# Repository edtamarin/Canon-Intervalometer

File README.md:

# DeltaShot

This is an intervalometer based on an ESP32 for remote shutter control of a DLSR camera. Currently the device is built for Canon bodies.

## Features

The Canon bodies are triggered by shorting the focus or the shutter pin to ground. Older versions use an N3 connector whereas newer ones use a standard jack.

The DeltaShot offers a 3.5mm jack output to interface with the camera. It is possible to trigger the camera manually at all times using two pushbutton switches on the device. However, these switches can also be triggered using the onboard ESP32 controller.

The software for the ESP32 is currently in development.

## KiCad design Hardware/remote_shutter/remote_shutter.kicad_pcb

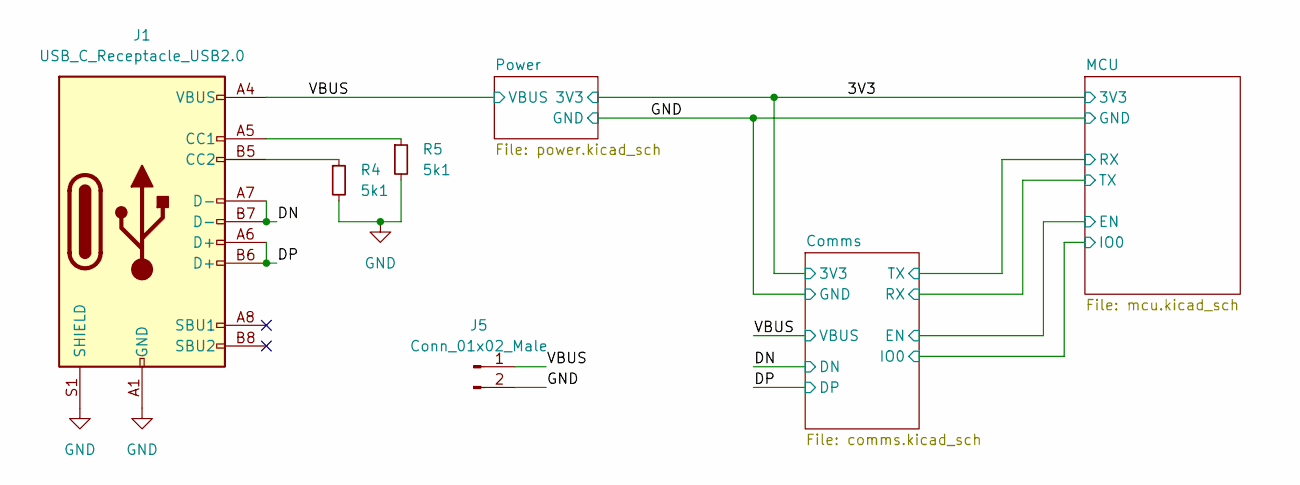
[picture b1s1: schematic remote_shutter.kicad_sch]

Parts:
J1: USB_C_Receptacle_USB2.0; USB_C_Receptacle_XKB_U262-16XN-4BVC11
J5: Conn_01x02_Male; PinHeader_1x02_P2.54mm_Vertical
R4, R5: 5k1; R_0603_1608Metric_Pad0.98x0.95mm_HandSolder

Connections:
/DN: J1.A7 (D-), J1.B7 (D-); also elsewhere on the board
/DP: J1.A6 (D+), J1.B6 (D+); also elsewhere on the board
/VBUS: J1.A4 (VBUS), J1.A9 (VBUS), J1.B4 (VBUS), J1.B9 (VBUS), J5.1; also elsewhere on the board
GND: J1.A1 (GND), J1.A12 (GND), J1.B1 (GND), J1.B12 (GND), J1.S1 (SHIELD), J5.2, R4.2, R5.2; also elsewhere on the board
unnamed: J1.A5 (CC1), R5.1
unnamed: J1.B5 (CC2), R4.1

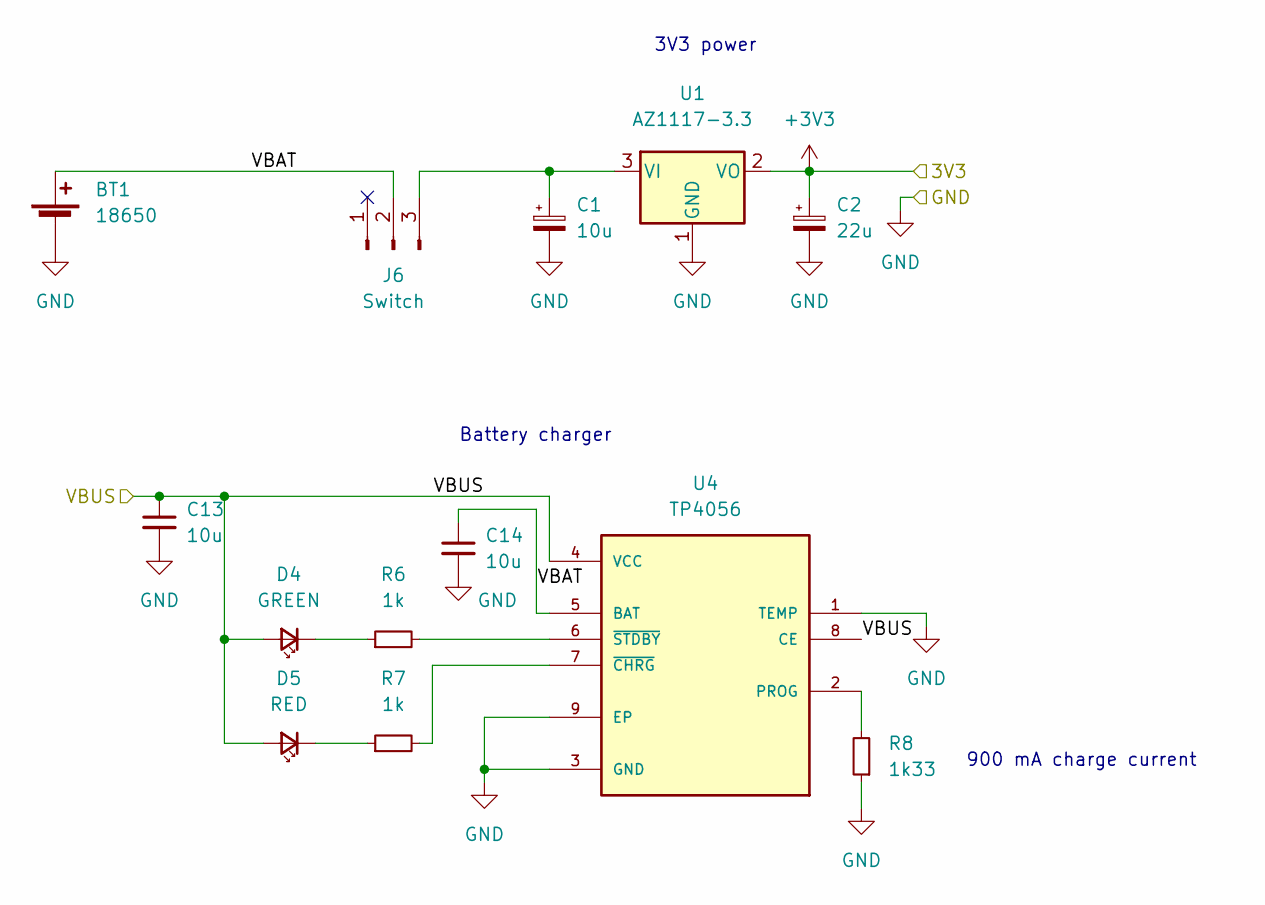
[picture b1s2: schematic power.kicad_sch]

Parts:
BT1: 18650; PinHeader_1x02_P2.54mm_Vertical
C1: 10u; CP_EIA-3528-21_Kemet-B_Pad1.50x2.35mm_HandSolder
C2: 22u; CP_EIA-3528-21_Kemet-B_Pad1.50x2.35mm_HandSolder
C13, C14: 10u; C_0805_2012Metric_Pad1.18x1.45mm_HandSolder
D4: GREEN; LED_0603_1608Metric_Pad1.05x0.95mm_HandSolder
D5: RED; LED_0603_1608Metric_Pad1.05x0.95mm_HandSolder
J6: Switch; PinHeader_1x03_P2.54mm_Vertical
R6, R7: 1k; R_0603_1608Metric_Pad0.98x0.95mm_HandSolder
R8: 1k33; R_0603_1608Metric_Pad0.98x0.95mm_HandSolder
U1: AZ1117-3.3; SOT-223-3_TabPin2
U4: TP4056; SOP127P600X175-9N

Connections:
+3V3: C2.1, U1.2 (VO); also elsewhere on the board
/Power/VBAT: BT1.1 (+), C14.1, J6.2, U4.5 (BAT)
/VBUS: C13.1, D4.2 (A), D5.2 (A), U4.4 (VCC), U4.8 (CE); also elsewhere on the board
GND: BT1.2 (-), C1.2, C2.2, C13.2, C14.2, R8.1, U1.1 (GND), U4.1 (TEMP), U4.3 (GND), U4.9 (EP); also elsewhere on the board
unnamed: C1.1, J6.3, U1.3 (VI)
unnamed: D4.1 (K), R6.1
unnamed: D5.1 (K), R7.1
unnamed: R6.2, U4.6 (~STDBY)
unnamed: R7.2, U4.7 (~CHRG)
unnamed: R8.2, U4.2 (PROG)

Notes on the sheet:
3V3 power
900 mA charge current
Battery charger

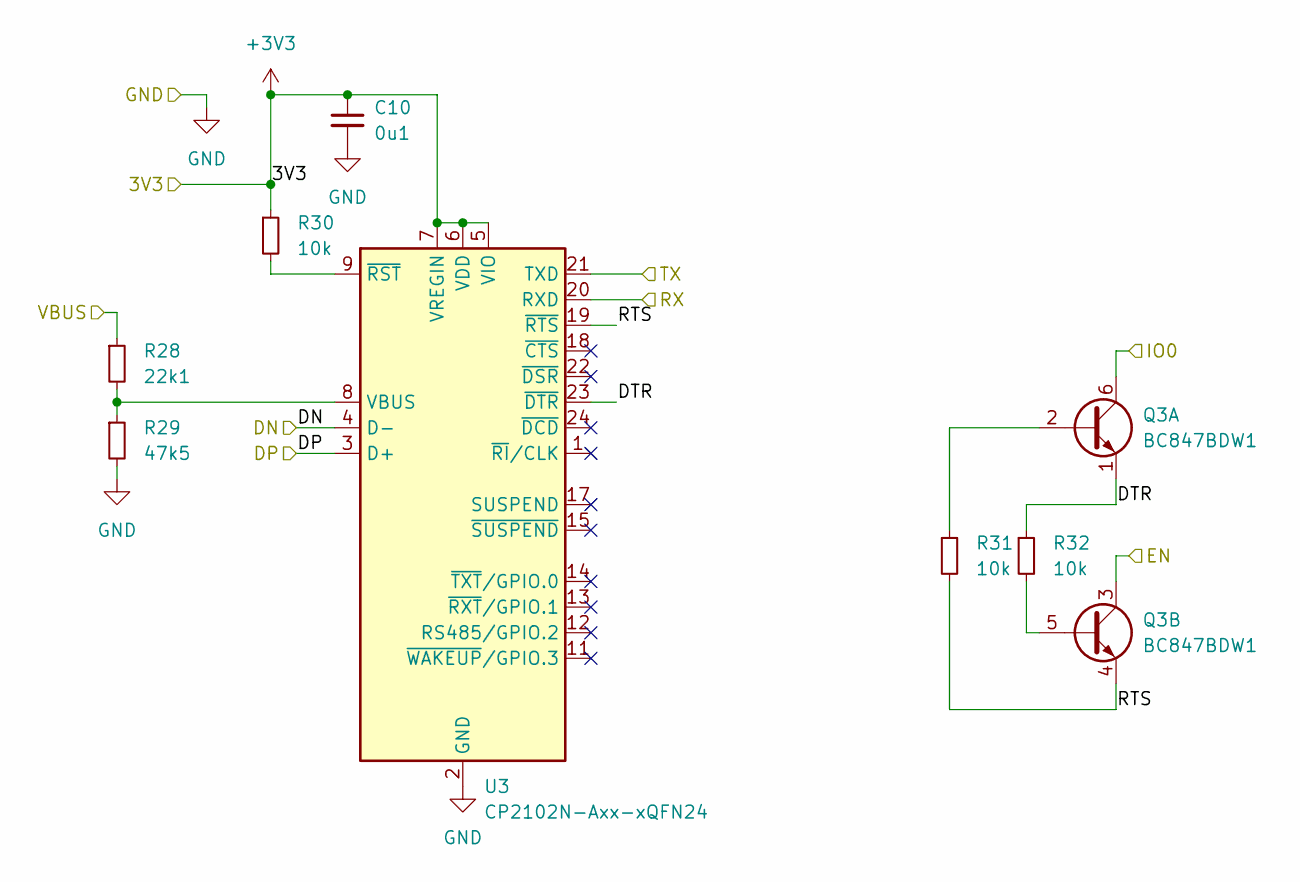
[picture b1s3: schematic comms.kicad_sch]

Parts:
C10: 0u1; C_0603_1608Metric_Pad1.08x0.95mm_HandSolder
Q3: BC847BDW1; SOT-363_SC-70-6
R28: 22k1; R_0603_1608Metric_Pad0.98x0.95mm_HandSolder
R29: 47k5; R_0603_1608Metric_Pad0.98x0.95mm_HandSolder
R30, R31, R32: 10k; R_0603_1608Metric_Pad0.98x0.95mm_HandSolder
U3: CP2102N-Axx-xQFN24; QFN-24-1EP_4x4mm_P0.5mm_EP2.6x2.6mm

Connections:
+3V3: C10.1, R30.1, U3.5 (VIO), U3.6 (VDD), U3.7 (VREGIN); also elsewhere on the board
/Comms/DTR: Q3.1 (E1), R32.1, U3.23 (~DTR)
/Comms/RTS: Q3.4 (E2), R31.2, U3.19 (~RTS)
/DN: U3.4 (D-); also elsewhere on the board
/DP: U3.3 (D+); also elsewhere on the board
/MCU/EN: Q3.3 (C2); also elsewhere on the board
/MCU/IO0: Q3.6 (C1); also elsewhere on the board
/MCU/RX: U3.21 (TXD); also elsewhere on the board
/MCU/TX: U3.20 (RXD); also elsewhere on the board
/VBUS: R28.1; also elsewhere on the board
GND: C10.2, R29.2, U3.2 (GND), U3.25 (GND); also elsewhere on the board
unnamed: Q3.2 (B1), R31.1
unnamed: Q3.5 (B2), R32.2
unnamed: R28.2, R29.1, U3.8 (VBUS)
unnamed: R30.2, U3.9 (~RST)

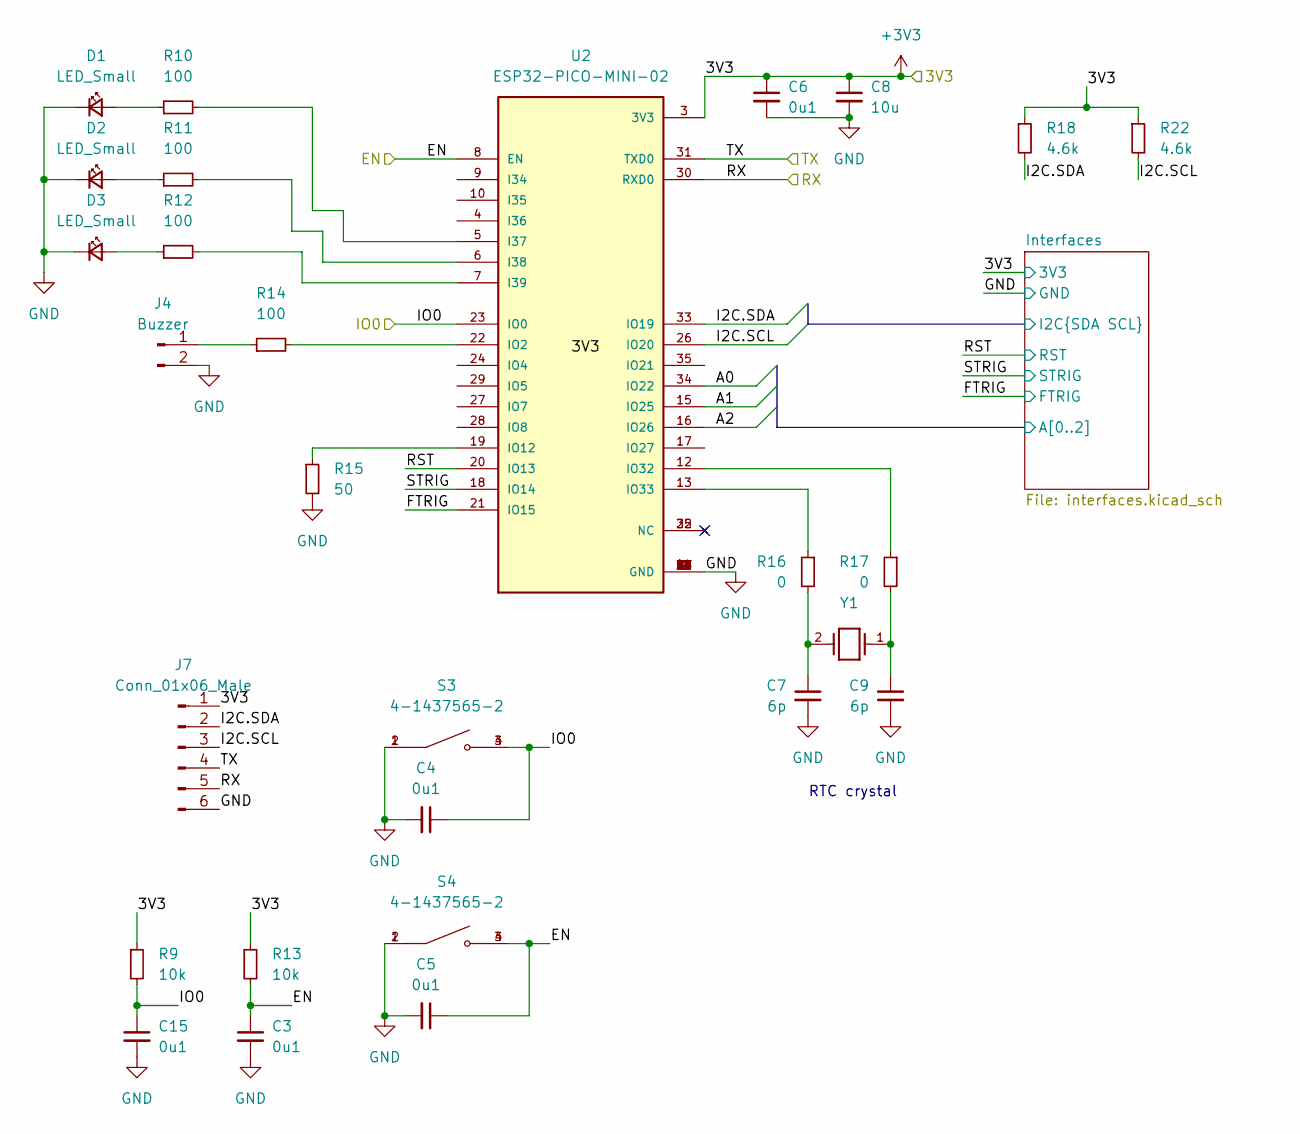
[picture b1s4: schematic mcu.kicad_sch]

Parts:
C3, C4, C5, C6, C15: 0u1; C_0603_1608Metric_Pad1.08x0.95mm_HandSolder
C7, C9: 6p; C_0603_1608Metric_Pad1.08x0.95mm_HandSolder
C8: 10u; C_0805_2012Metric_Pad1.18x1.45mm_HandSolder
D1, D2, D3: LED_Small; LED_0603_1608Metric_Pad1.05x0.95mm_HandSolder
J4: Buzzer; PinSocket_1x02_P2.54mm_Vertical
J7: Conn_01x06_Male; PinHeader_1x06_P2.54mm_Vertical
R9, R13: 10k; R_0603_1608Metric_Pad0.98x0.95mm_HandSolder
R10, R11, R12, R14: 100; R_0603_1608Metric_Pad0.98x0.95mm_HandSolder
R15: 50; R_0603_1608Metric_Pad0.98x0.95mm_HandSolder
R16, R17: 0; R_0603_1608Metric_Pad0.98x0.95mm_HandSolder
R18, R22: 4.6k; R_0603_1608Metric_Pad0.98x0.95mm_HandSolder
S3, S4: 4-1437565-2; SW_4-1437565-2
U2: ESP32-PICO-MINI-02; MODULE_ESP32-PICO-MINI-02; PARTREV v1.0
Y1: NX3215SA-32.768K-STD-MUA-14; XTAL_NX3215SA-32.768K-STD-MUA-14; PARTREV --

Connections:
+3V3: C6.1, C8.1, J7.1, R9.1, R13.1, R18.1, R22.1, U2.3 (3V3); also elsewhere on the board
/MCU/EN: C3.1, C5.1, R13.2, S4.3, S4.4, U2.8 (EN); also elsewhere on the board
/MCU/FTRIG: U2.21 (IO15); also elsewhere on the board
/MCU/IO0: C4.1, C15.1, R9.2, S3.3, S3.4, U2.23 (IO0); also elsewhere on the board
/MCU/Interfaces/A0: U2.34 (IO22); also elsewhere on the board
/MCU/Interfaces/A1: U2.15 (IO25); also elsewhere on the board
/MCU/Interfaces/A2: U2.16 (IO26); also elsewhere on the board
/MCU/Interfaces/I2C.SCL: J7.3, R22.2, U2.26 (IO20); also elsewhere on the board
/MCU/Interfaces/I2C.SDA: J7.2, R18.2, U2.33 (IO19); also elsewhere on the board
/MCU/RST: U2.20 (IO13); also elsewhere on the board
/MCU/RX: J7.5, U2.30 (RXD0); also elsewhere on the board
/MCU/STRIG: U2.18 (IO14); also elsewhere on the board
/MCU/TX: J7.4, U2.31 (TXD0); also elsewhere on the board
GND: C3.2, C4.2, C5.2, C6.2, C7.2, C8.2, C9.2, C15.2, D1.1 (K), D2.1 (K), D3.1 (K), J4.2, J7.6, R15.2, S3.1, S3.2, S4.1, S4.2, U2.1 (GND), U2.2 (GND), U2.11 (GND), U2.14 (GND), U2.36 (GND), U2.37 (GND), U2.38 (GND), U2.39 (GND), U2.40 (GND), U2.41 (GND), U2.42 (GND), U2.43 (GND), U2.44 (GND), U2.45 (GND), U2.46 (GND), U2.47 (GND), U2.48 (GND), U2.49 (GND), U2.50 (GND), U2.51 (GND), U2.52 (GND), U2.53 (GND), U2.54 (GND), U2.55 (GND), U2.56 (GND), U2.57 (GND), U2.58 (GND), U2.59 (GND), U2.60 (GND), U2.61 (GND); also elsewhere on the board
unnamed: C7.1, R16.2, Y1.2
unnamed: C9.1, R17.2, Y1.1
unnamed: D1.2 (A), R10.1
unnamed: D2.2 (A), R11.1
unnamed: D3.2 (A), R12.1
unnamed: J4.1, R14.1
unnamed: R10.2, U2.5 (I37)
unnamed: R11.2, U2.6 (I38)
unnamed: R12.2, U2.7 (I39)
unnamed: R14.2, U2.22 (IO2)
unnamed: R15.1, U2.19 (IO12)
unnamed: R16.1, U2.13 (IO33)
unnamed: R17.1, U2.12 (IO32)

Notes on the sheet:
RTC crystal

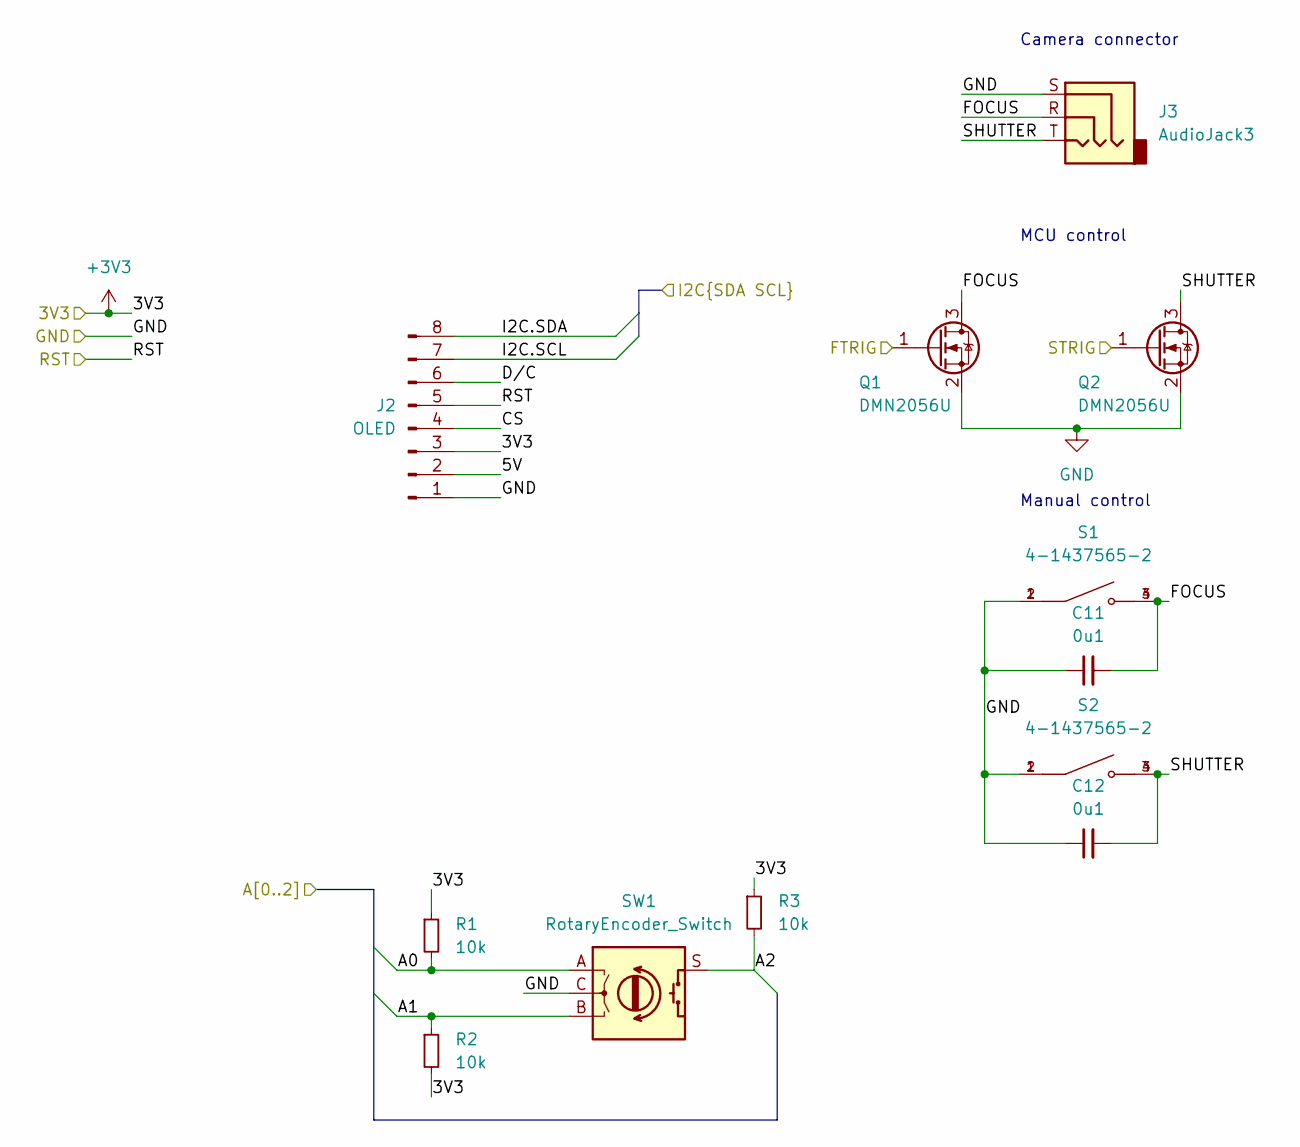
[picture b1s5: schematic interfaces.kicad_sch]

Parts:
C11, C12: 0u1; C_0603_1608Metric_Pad1.08x0.95mm_HandSolder
J2: OLED; PinSocket_1x08_P2.54mm_Vertical
J3: AudioJack3; PJ-320B
Q1, Q2: DMN2056U; SOT-23
R1, R2, R3: 10k; R_0603_1608Metric_Pad0.98x0.95mm_HandSolder
S1, S2: 4-1437565-2; SW_4-1437565-2
SW1: RotaryEncoder_Switch; SIQ-02FVS3

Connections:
+3V3: J2.3, R1.1, R2.2, R3.1; also elsewhere on the board
/MCU/FTRIG: Q1.1 (G); also elsewhere on the board
/MCU/Interfaces/5V: J2.2
/MCU/Interfaces/A0: R1.2, SW1.A; also elsewhere on the board
/MCU/Interfaces/A1: R2.1, SW1.B; also elsewhere on the board
/MCU/Interfaces/A2: R3.2, SW1.S; also elsewhere on the board
/MCU/Interfaces/CS: J2.4
/MCU/Interfaces/D/C: J2.6
/MCU/Interfaces/FOCUS: C11.2, J3.R, Q1.3 (D), S1.3, S1.4
/MCU/Interfaces/I2C.SCL: J2.7; also elsewhere on the board
/MCU/Interfaces/I2C.SDA: J2.8; also elsewhere on the board
/MCU/Interfaces/SHUTTER: C12.2, J3.T, Q2.3 (D), S2.3, S2.4
/MCU/RST: J2.5; also elsewhere on the board
/MCU/STRIG: Q2.1 (G); also elsewhere on the board
GND: C11.1, C12.1, J2.1, J3.S, Q1.2 (S), Q2.2 (S), S1.1, S1.2, S2.1, S2.2, SW1.C; also elsewhere on the board

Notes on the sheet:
MCU control
Manual control
Camera connector

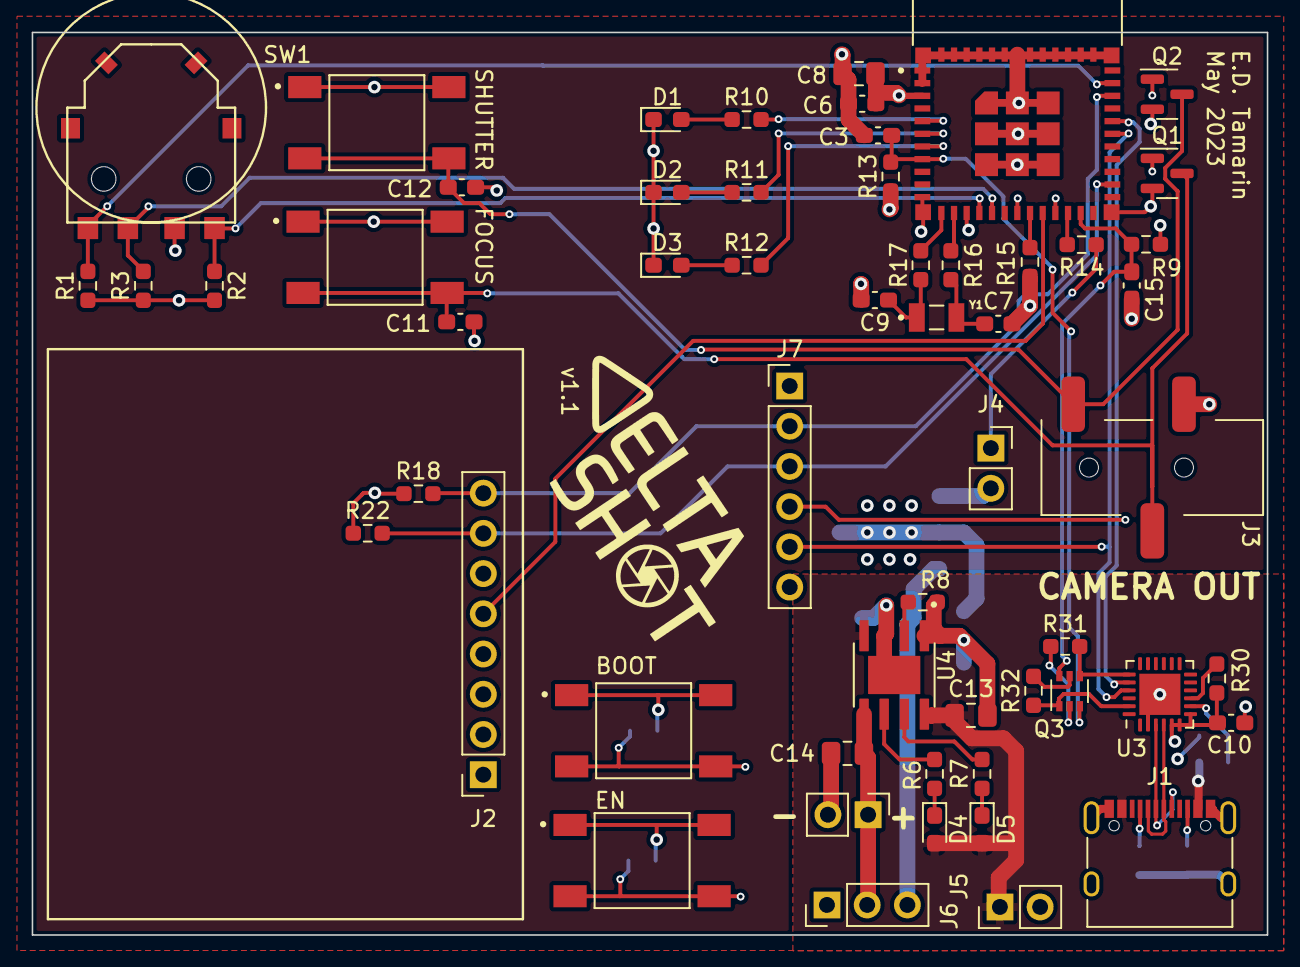
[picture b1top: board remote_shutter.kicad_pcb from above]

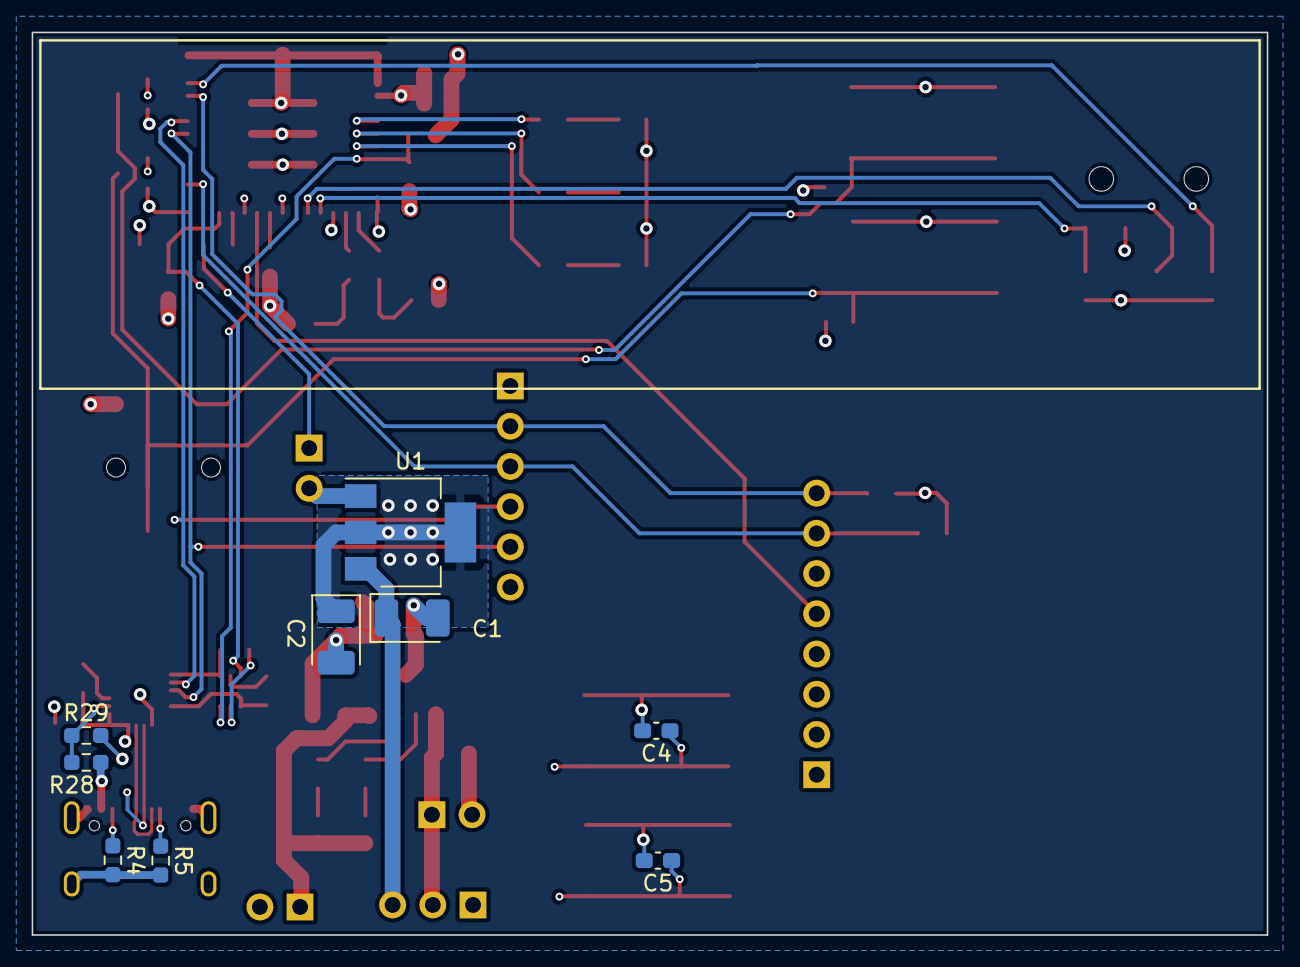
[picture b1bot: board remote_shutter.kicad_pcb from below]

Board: 4 copper layers, 78.0 x 57.0 mm, 65 parts (9 on the bottom side), 47 nets.

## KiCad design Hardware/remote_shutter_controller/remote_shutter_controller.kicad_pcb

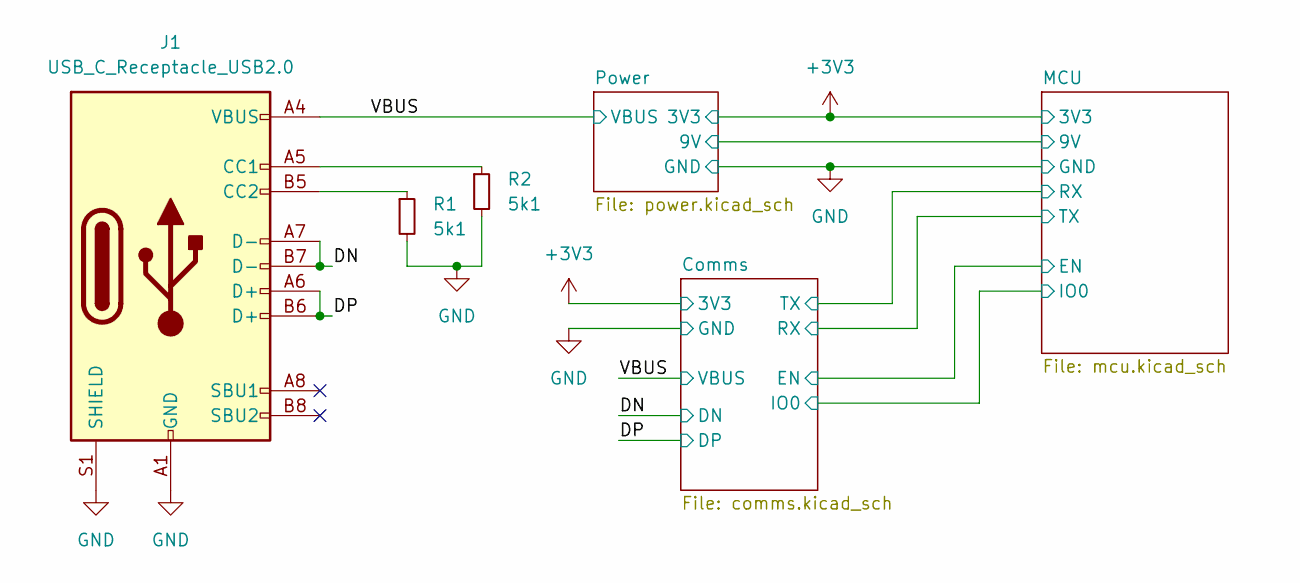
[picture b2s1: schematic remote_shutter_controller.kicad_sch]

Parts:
J1: USB_C_Receptacle_USB2.0; USB_C_Receptacle_XKB_U262-16XN-4BVC11
R1, R2: 5k1; R_0603_1608Metric_Pad0.98x0.95mm_HandSolder

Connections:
/DN: J1.A7 (D-), J1.B7 (D-); also elsewhere on the board
/DP: J1.A6 (D+), J1.B6 (D+); also elsewhere on the board
/VBUS: J1.A4 (VBUS), J1.A9 (VBUS), J1.B4 (VBUS), J1.B9 (VBUS); also elsewhere on the board
GND: J1.A1 (GND), J1.A12 (GND), J1.B1 (GND), J1.B12 (GND), J1.S1 (SHIELD), R1.2, R2.2; also elsewhere on the board
unnamed: J1.A5 (CC1), R2.1
unnamed: J1.B5 (CC2), R1.1

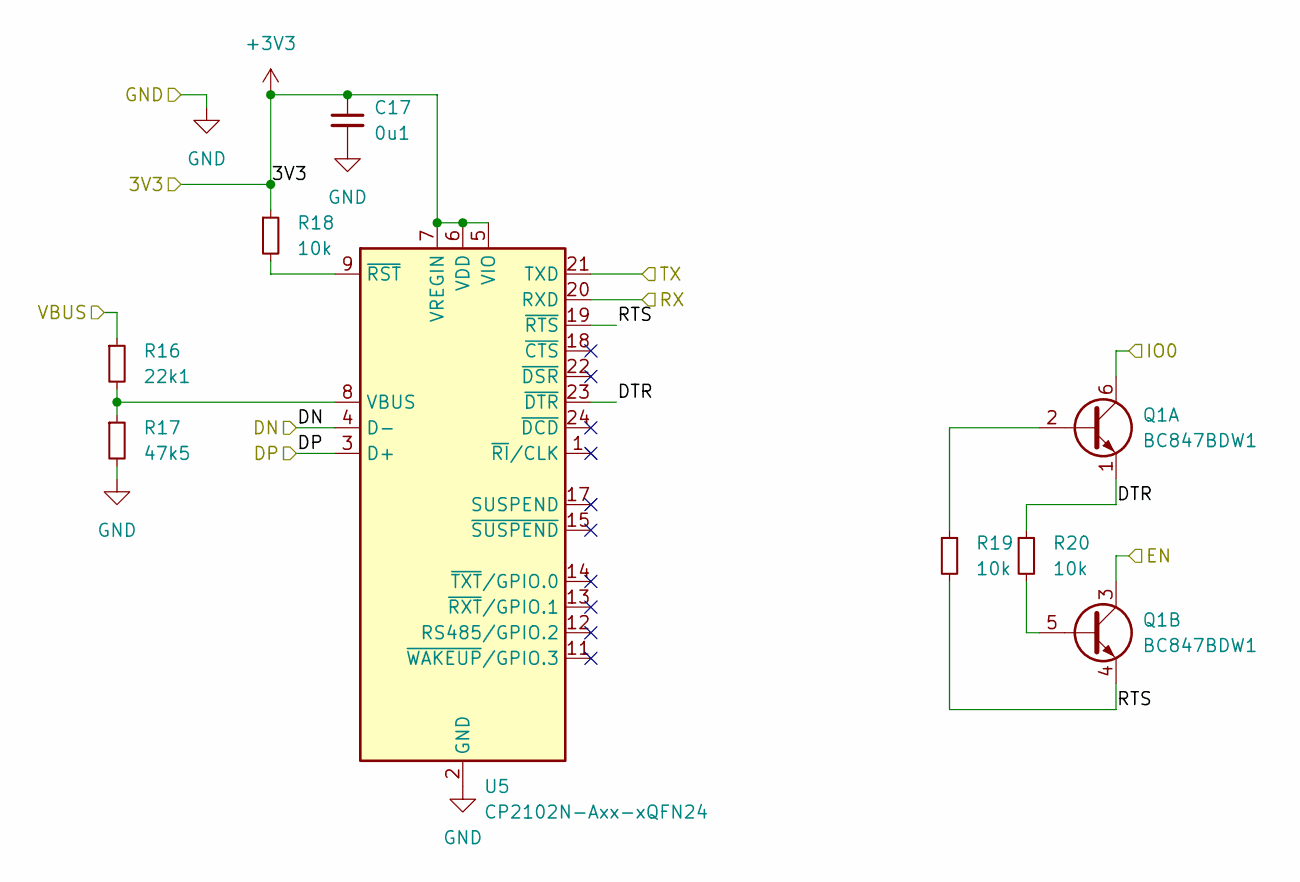
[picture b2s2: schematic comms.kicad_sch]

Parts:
C17: 0u1; C_0603_1608Metric_Pad1.08x0.95mm_HandSolder
Q1: BC847BDW1; SOT-363_SC-70-6
R16: 22k1; R_0603_1608Metric_Pad0.98x0.95mm_HandSolder
R17: 47k5; R_0603_1608Metric_Pad0.98x0.95mm_HandSolder
R18, R19, R20: 10k; R_0603_1608Metric_Pad0.98x0.95mm_HandSolder
U5: CP2102N-Axx-xQFN24; QFN-24-1EP_4x4mm_P0.5mm_EP2.6x2.6mm

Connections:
+3V3: C17.1, R18.1, U5.5 (VIO), U5.6 (VDD), U5.7 (VREGIN); also elsewhere on the board
/Comms/DTR: Q1.1 (E1), R20.1, U5.23 (~DTR)
/Comms/RTS: Q1.4 (E2), R19.2, U5.19 (~RTS)
/Comms/RX: U5.20 (RXD); also elsewhere on the board
/Comms/TX: U5.21 (TXD); also elsewhere on the board
/DN: U5.4 (D-); also elsewhere on the board
/DP: U5.3 (D+); also elsewhere on the board
/MCU/EN: Q1.3 (C2); also elsewhere on the board
/MCU/IO0: Q1.6 (C1); also elsewhere on the board
/VBUS: R16.1; also elsewhere on the board
GND: C17.2, R17.2, U5.2 (GND), U5.25 (GND); also elsewhere on the board
unnamed: Q1.2 (B1), R19.1
unnamed: Q1.5 (B2), R20.2
unnamed: R16.2, R17.1, U5.8 (VBUS)
unnamed: R18.2, U5.9 (~RST)

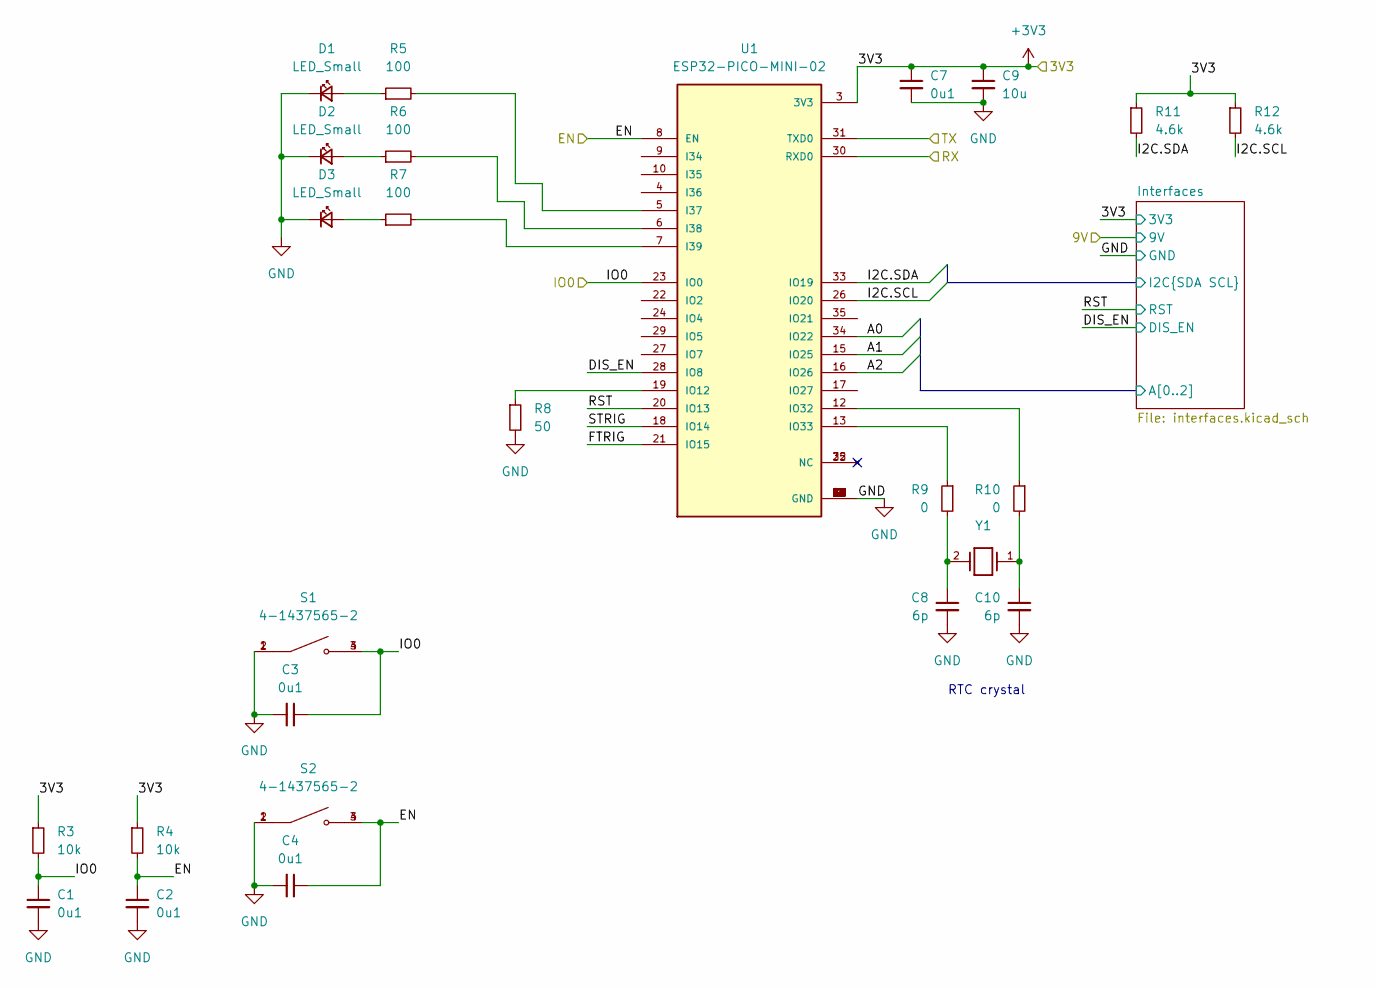
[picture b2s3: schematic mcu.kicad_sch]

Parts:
C1, C2, C3, C4, C7: 0u1; C_0603_1608Metric_Pad1.08x0.95mm_HandSolder
C8, C10: 6p; C_0603_1608Metric_Pad1.08x0.95mm_HandSolder
C9: 10u; C_0805_2012Metric_Pad1.18x1.45mm_HandSolder
D1, D2, D3: LED_Small; LED_0603_1608Metric_Pad1.05x0.95mm_HandSolder
R3, R4: 10k; R_0603_1608Metric_Pad0.98x0.95mm_HandSolder
R5, R6, R7: 100; R_0603_1608Metric_Pad0.98x0.95mm_HandSolder
R8: 50; R_0603_1608Metric_Pad0.98x0.95mm_HandSolder
R9, R10: 0; R_0603_1608Metric_Pad0.98x0.95mm_HandSolder
R11, R12: 4.6k; R_0603_1608Metric_Pad0.98x0.95mm_HandSolder
S1, S2: 4-1437565-2; SW_4-1437565-2
U1: ESP32-PICO-MINI-02; MODULE_ESP32-PICO-MINI-02; PARTREV v1.0
Y1: NX3215SA-32.768K-STD-MUA-14; XTAL_NX3215SA-32.768K-STD-MUA-14; PARTREV --

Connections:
+3V3: C7.1, C9.1, R3.1, R4.1, R11.1, R12.1, U1.3 (3V3); also elsewhere on the board
/Comms/RX: U1.31 (TXD0); also elsewhere on the board
/Comms/TX: U1.30 (RXD0); also elsewhere on the board
/MCU/DIS_EN: U1.28 (IO8); also elsewhere on the board
/MCU/EN: C2.1, C4.1, R4.2, S2.3, S2.4, U1.8 (EN); also elsewhere on the board
/MCU/FTRIG: U1.21 (IO15)
/MCU/IO0: C1.1, C3.1, R3.2, S1.3, S1.4, U1.23 (IO0); also elsewhere on the board
/MCU/Interfaces/A0: U1.34 (IO22); also elsewhere on the board
/MCU/Interfaces/A1: U1.15 (IO25); also elsewhere on the board
/MCU/Interfaces/A2: U1.16 (IO26); also elsewhere on the board
/MCU/Interfaces/I2C.SCL: R12.2, U1.26 (IO20); also elsewhere on the board
/MCU/Interfaces/I2C.SDA: R11.2, U1.33 (IO19); also elsewhere on the board
/MCU/RST: U1.20 (IO13); also elsewhere on the board
/MCU/STRIG: U1.18 (IO14)
GND: C1.2, C2.2, C3.2, C4.2, C7.2, C8.2, C9.2, C10.2, D1.1 (K), D2.1 (K), D3.1 (K), R8.2, S1.1, S1.2, S2.1, S2.2, U1.1 (GND), U1.2 (GND), U1.11 (GND), U1.14 (GND), U1.36 (GND), U1.37 (GND), U1.38 (GND), U1.39 (GND), U1.40 (GND), U1.41 (GND), U1.42 (GND), U1.43 (GND), U1.44 (GND), U1.45 (GND), U1.46 (GND), U1.47 (GND), U1.48 (GND), U1.49 (GND), U1.50 (GND), U1.51 (GND), U1.52 (GND), U1.53 (GND), U1.54 (GND), U1.55 (GND), U1.56 (GND), U1.57 (GND), U1.58 (GND), U1.59 (GND), U1.60 (GND), U1.61 (GND); also elsewhere on the board
unnamed: C8.1, R9.2, Y1.2
unnamed: C10.1, R10.2, Y1.1
unnamed: D1.2 (A), R5.1
unnamed: D2.2 (A), R6.1
unnamed: D3.2 (A), R7.1
unnamed: R5.2, U1.5 (I37)
unnamed: R6.2, U1.6 (I38)
unnamed: R7.2, U1.7 (I39)
unnamed: R8.1, U1.19 (IO12)
unnamed: R9.1, U1.13 (IO33)
unnamed: R10.1, U1.12 (IO32)

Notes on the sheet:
RTC crystal

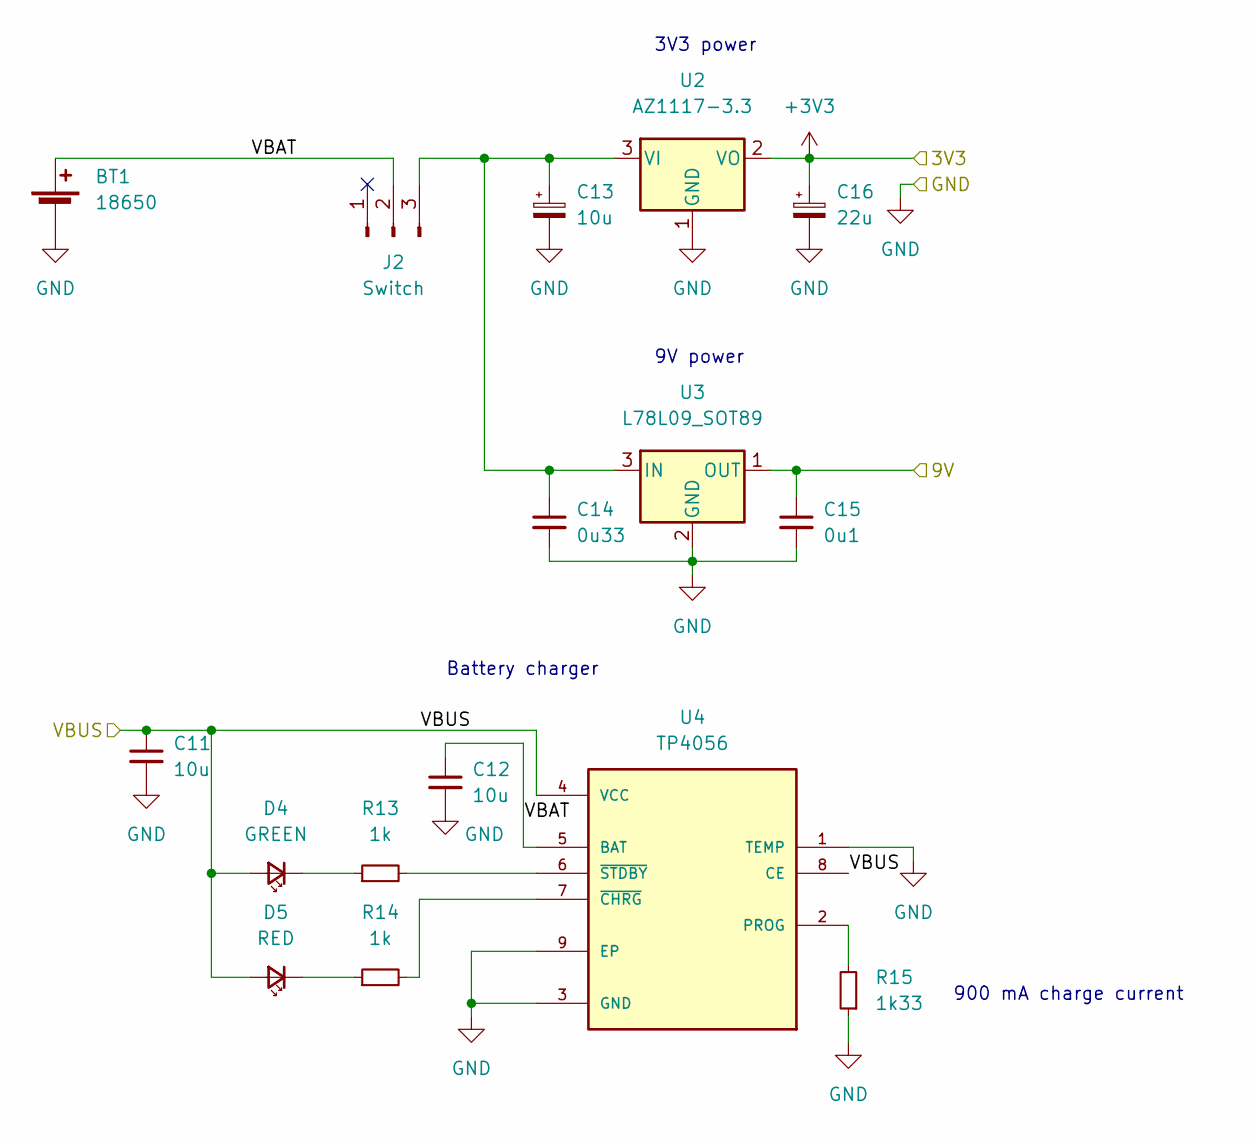
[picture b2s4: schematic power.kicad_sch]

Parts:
BT1: 18650; JST_PH_S2B-PH-K_1x02_P2.00mm_Horizontal
C11, C12: 10u; C_0805_2012Metric_Pad1.18x1.45mm_HandSolder
C13: 10u; CP_EIA-3528-21_Kemet-B_Pad1.50x2.35mm_HandSolder
C14: 0u33; C_0805_2012Metric_Pad1.18x1.45mm_HandSolder
C15: 0u1; C_0805_2012Metric_Pad1.18x1.45mm_HandSolder
C16: 22u; CP_EIA-3528-21_Kemet-B_Pad1.50x2.35mm_HandSolder
D4: GREEN; LED_0603_1608Metric_Pad1.05x0.95mm_HandSolder
D5: RED; LED_0603_1608Metric_Pad1.05x0.95mm_HandSolder
J2: Switch; PinHeader_1x03_P2.54mm_Vertical
R13, R14: 1k; R_0603_1608Metric_Pad0.98x0.95mm_HandSolder
R15: 1k33; R_0603_1608Metric_Pad0.98x0.95mm_HandSolder
U2: AZ1117-3.3; SOT-223-3_TabPin2
U3: L78L09_SOT89; SOT-89-3
U4: TP4056; SOP127P600X175-9N

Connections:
+3V3: C16.1, U2.2 (VO); also elsewhere on the board
/MCU/9V: C15.1, U3.1 (OUT); also elsewhere on the board
/Power/VBAT: BT1.1 (+), C12.1, J2.2, U4.5 (BAT)
/VBUS: C11.1, D4.2 (A), D5.2 (A), U4.4 (VCC), U4.8 (CE); also elsewhere on the board
GND: BT1.2 (-), C11.2, C12.2, C13.2, C14.2, C15.2, C16.2, R15.1, U2.1 (GND), U3.2 (GND), U4.1 (TEMP), U4.3 (GND), U4.9 (EP); also elsewhere on the board
unnamed: C13.1, C14.1, J2.3, U2.3 (VI), U3.3 (IN)
unnamed: D4.1 (K), R13.1
unnamed: D5.1 (K), R14.1
unnamed: R13.2, U4.6 (~STDBY)
unnamed: R14.2, U4.7 (~CHRG)
unnamed: R15.2, U4.2 (PROG)

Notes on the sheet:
Battery charger
9V power
3V3 power
900 mA charge current

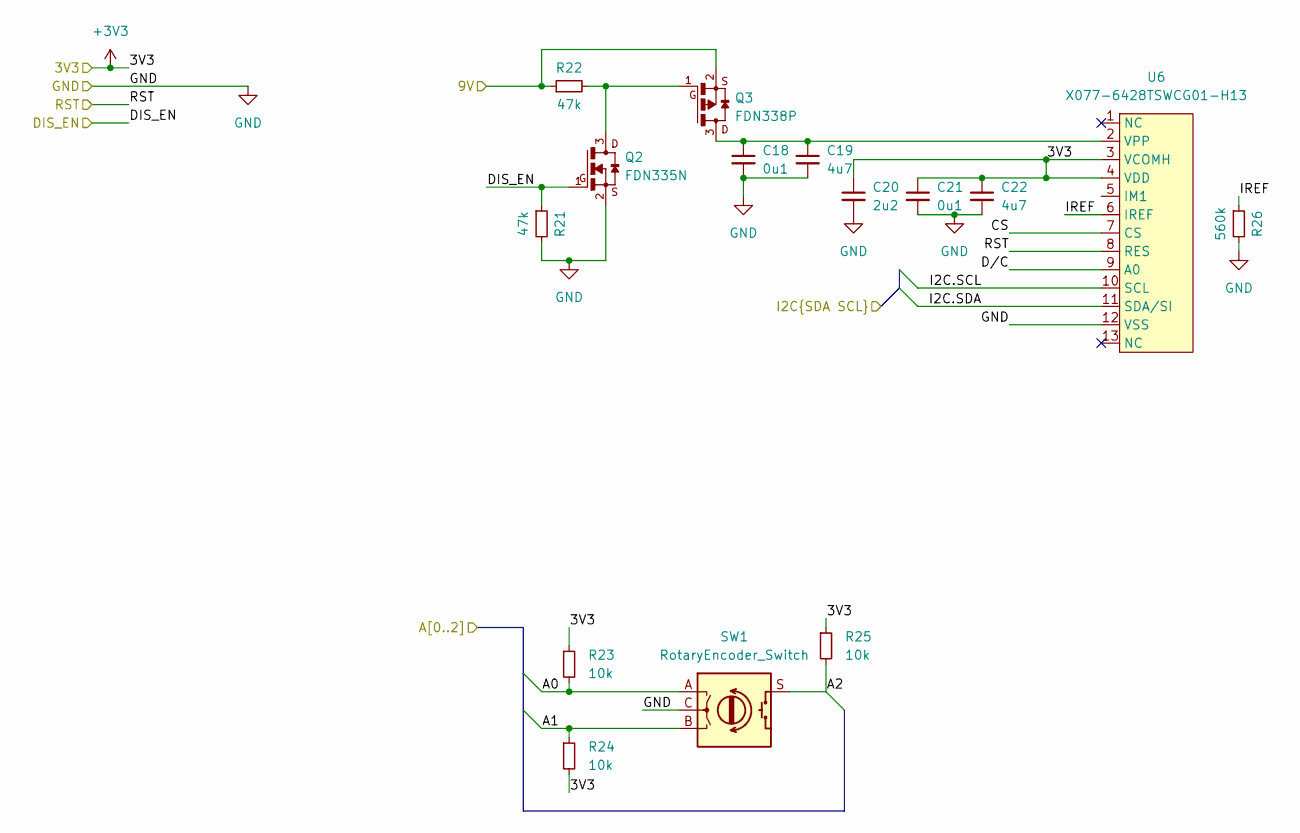
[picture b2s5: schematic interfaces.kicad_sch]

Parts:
C18, C21: 0u1; C_0603_1608Metric_Pad1.08x0.95mm_HandSolder
C19, C22: 4u7; C_0603_1608Metric_Pad1.08x0.95mm_HandSolder
C20: 2u2; C_0603_1608Metric_Pad1.08x0.95mm_HandSolder
Q2: FDN335N; SSOT-3
Q3: FDN338P; SSOT-3
R21, R22: 47k; R_0603_1608Metric_Pad0.98x0.95mm_HandSolder
R23, R24, R25: 10k; R_0603_1608Metric_Pad0.98x0.95mm_HandSolder
R26: 560k; R_0603_1608Metric_Pad0.98x0.95mm_HandSolder
SW1: RotaryEncoder_Switch; SIQ-02FVS3
U6: X077-6428TSWCG01-H13

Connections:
+3V3: C20.1, C21.1, C22.1, R23.1, R24.2, R25.1, U6.3 (VCOMH), U6.4 (VDD); also elsewhere on the board
/MCU/9V: Q3.2, R22.1; also elsewhere on the board
/MCU/DIS_EN: Q2.1, R21.1; also elsewhere on the board
/MCU/Interfaces/A0: R23.2, SW1.A; also elsewhere on the board
/MCU/Interfaces/A1: R24.1, SW1.B; also elsewhere on the board
/MCU/Interfaces/A2: R25.2, SW1.S; also elsewhere on the board
/MCU/Interfaces/CS: U6.7 (CS)
/MCU/Interfaces/D/C: U6.9 (A0)
/MCU/Interfaces/I2C.SCL: U6.10 (SCL); also elsewhere on the board
/MCU/Interfaces/I2C.SDA: U6.11 (SDA/SI); also elsewhere on the board
/MCU/Interfaces/IREF: R26.1, U6.6 (IREF)
/MCU/RST: U6.8 (RES); also elsewhere on the board
GND: C18.2, C19.2, C20.2, C21.2, C22.2, Q2.2, R21.2, R26.2, SW1.C, U6.12 (VSS); also elsewhere on the board
unnamed: C18.1, C19.1, Q3.3, U6.2 (VPP)
unnamed: Q2.3, Q3.1, R22.2
